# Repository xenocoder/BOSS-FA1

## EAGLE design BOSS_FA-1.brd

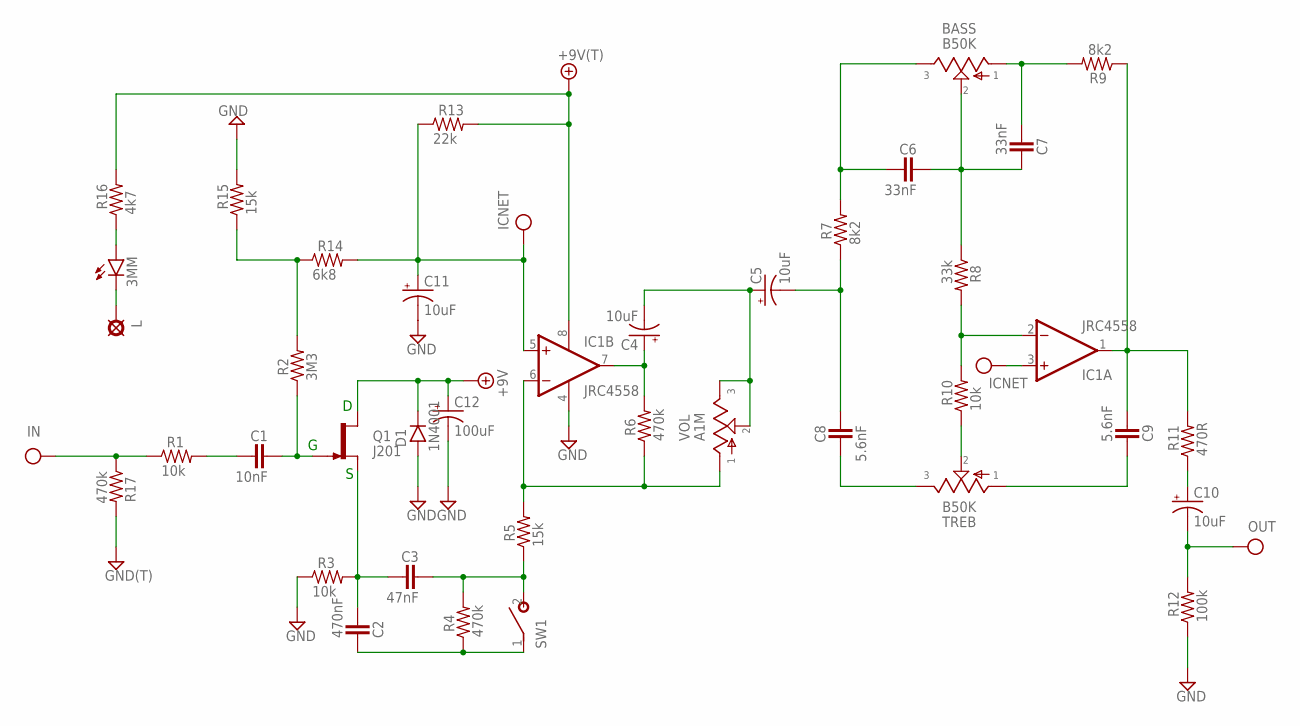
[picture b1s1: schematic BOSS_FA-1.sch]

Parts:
3MM: LED3MM
+9V: +9V(T); SQUARE
BASS: B50K; 16MM_PCB_PADS
C1: 10nF; 072X025
C2: 470nF; 072X035
C3: 47nF; 072X025
C4, C5, C10, C11: 10uF; 050_020_1
C6, C7: 33nF; 072X025
C8, C9: 5.6nF; 072X025
C12: 100uF; 063_025
D1: 1N4001; DO41-3
G: GND(T); SQUARE
IC1: JRC4558; DIL08
IN: IN(T); SQUARE
L: PAD; SQUARE
OUT: OUT(T); SQUARE
Q1: J201; TO92-
R1, R3, R10: 10k; R0207/3
R2: 3M3; R0207/3
R4, R6, R17: 470k; R0207/3
R5, R15: 15k; R0207/3
R7, R9: 8k2; R0207/3
R8: 33k; R0207/3
R11: 470R; R0207/3
R12: 100k; R0207/3
R13: 22k; R0207/3
R14: 6k8; R0207/3
R16: 4k7; R0207/3
SW1: SPST
TREB: B50K; 16MM_PCB_PADS
VOL: A1M; 16MM_PCB_PADS

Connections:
+9V: +9V.1, C12.+, D1.C, IC1.8 (V+), Q1.3 (D), R13.2, R16.2
A: C11.+, IC1.3 (+IN), IC1.5 (+IN), R13.1, R14.2
GND: C11.-, C12.-, D1.A, G.1, IC1.4 (V-), R3.1, R12.1, R15.2, R17.2
IN: IN.1, R1.1, R17.1
unnamed: C1.1, R1.2
unnamed: C1.2, Q1.1 (G), R2.1
unnamed: 3MM.A, R16.1
unnamed: R10.1, TREB.2
unnamed: C3.2, R4.2, R5.1, SW1.2 (S)
unnamed: C4.+, IC1.7 (OUT), R6.2
unnamed: IC1.6 (-IN), R5.2, R6.1, VOL.1
unnamed: 3MM.K (C), L.1
unnamed: C2.2, R4.1, SW1.1
unnamed: C2.1, C3.1, Q1.2 (S), R3.2
unnamed: C4.-, C5.+, VOL.2, VOL.3
unnamed: C5.-, C8.2, R7.1
unnamed: BASS.3, C6.1, R7.2
unnamed: BASS.2, C6.2, C7.2, R8.1
unnamed: BASS.1, C7.1, R9.2
unnamed: C9.1, IC1.1 (OUT), R9.1, R11.2
unnamed: IC1.2 (-IN), R8.2, R10.2
unnamed: C9.2, TREB.1
unnamed: C8.1, TREB.3
unnamed: C10.+, R11.1
unnamed: R2.2, R14.1, R15.1
OUT: C10.-, OUT.1, R12.2

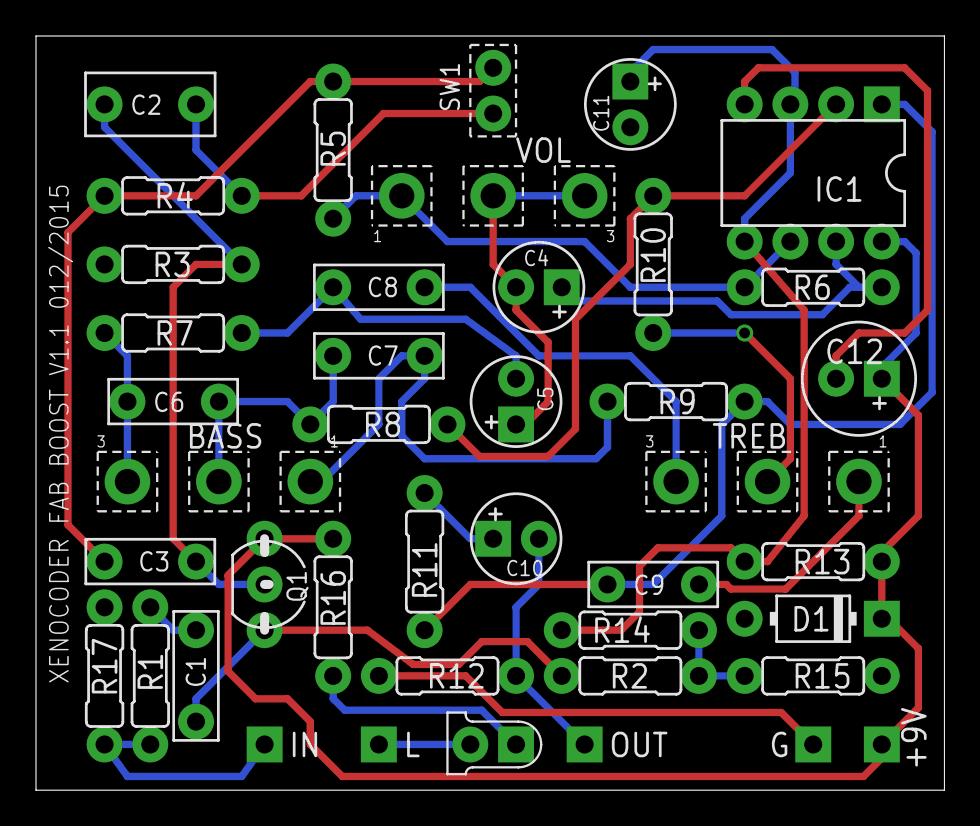
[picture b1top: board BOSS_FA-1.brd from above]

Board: 2 copper layers, 50.5 x 41.9 mm, 42 parts (0 on the bottom side), 26 nets.

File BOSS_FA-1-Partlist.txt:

Partlist

Exported from BOSS_FA-1.brd at 5/9/15 7:09 PM

EAGLE Version 7.2.0 Copyright (c) 1988-2014 CadSoft

Assembly variant: 

Part     Value          Package       Library         Position (inch)       Orientation

+9V      +9V(T)         SQUARE        mb_supply       (1.85 0.1)            R0
3MM      LED3MM         LED3MM        mb_diodes       (1 0.1)               R180
BASS     B50K           16MM_PCB_PADS mb_pots         (0.4 0.675)           R0
C1       10nF           072X025       mb_caps-box     (0.35 0.25)           R270
C2       470nF          072X035       mb_caps-box     (0.25 1.5)            R0
C3       47nF           072X025       mb_caps-box     (0.25 0.5)            R180
C4       10uF           050_020_1     mb_caps-electro (1.1 1.1)             R180
C5       10uF           050_020_1     mb_caps-electro (1.05 0.85)           R90
C6       33nF           072X025       mb_caps-box     (0.3 0.85)            R0
C7       33nF           072X025       mb_caps-box     (0.75 0.95)           R180
C8       5.6nF          072X025       mb_caps-box     (0.75 1.1)            R180
C9       5.6nF          072X025       mb_caps-box     (1.35 0.45)           R0
C10      10uF           050_020_1     mb_caps-electro (1.05 0.55)           R0
C11      10uF           050_020_1     mb_caps-electro (1.3 1.5)             R270
C12      100uF          063_025       mb_caps-electro (1.8 0.9)             R180
D1       1N4001         DO41-3        mb_diodes       (1.7 0.375)           R0
G        GND(T)         SQUARE        mb_supply       (1.7 0.1)             R0
IC1      JRC4558        DIL08         mb_ics          (1.7 1.35)            R180
IN       IN(T)          SQUARE        mb_supply       (0.5 0.1)             R0
L                       SQUARE        mb_supply       (0.75 0.1)            R0
OUT      OUT(T)         SQUARE        mb_supply       (1.2 0.1)             R0
Q1       J201           TO92-         mb_trans        (0.5 0.45)            R270
R1       10k            R0207/3       mb_resistors    (0.25 0.25)           R90
R2       3M3            R0207/3       mb_resistors    (1.3 0.25)            R0
R3       10k            R0207/3       mb_resistors    (0.3 1.15)            R0
R4       470k           R0207/3       mb_resistors    (0.3 1.3)             R180
R5       15k            R0207/3       mb_resistors    (0.65 1.4)            R270
R6       470k           R0207/3       mb_resistors    (1.7 1.1)             R0
R7       8k2            R0207/3       mb_resistors    (0.3 1)               R180
R8       33k            R0207/3       mb_resistors    (0.75 0.8)            R0
R9       8k2            R0207/3       mb_resistors    (1.4 0.85)            R180
R10      10k            R0207/3       mb_resistors    (1.35 1.15)           R90
R11      470R           R0207/3       mb_resistors    (0.85 0.5)            R270
R12      100k           R0207/3       mb_resistors    (0.9 0.25)            R0
R13      22k            R0207/3       mb_resistors    (1.7 0.5)             R0
R14      6k8            R0207/3       mb_resistors    (1.3 0.35)            R180
R15      15k            R0207/3       mb_resistors    (1.7 0.25)            R0
R16      4k7            R0207/3       mb_resistors    (0.65 0.4)            R90
R17      470k           R0207/3       mb_resistors    (0.15 0.25)           R90
SW1      SPST           SPST          mb_switches     (1 1.53)              R90
TREB     B50K           16MM_PCB_PADS mb_pots         (1.6 0.675)           R0
VOL      A1M            16MM_PCB_PADS mb_pots         (1 1.3)               R180

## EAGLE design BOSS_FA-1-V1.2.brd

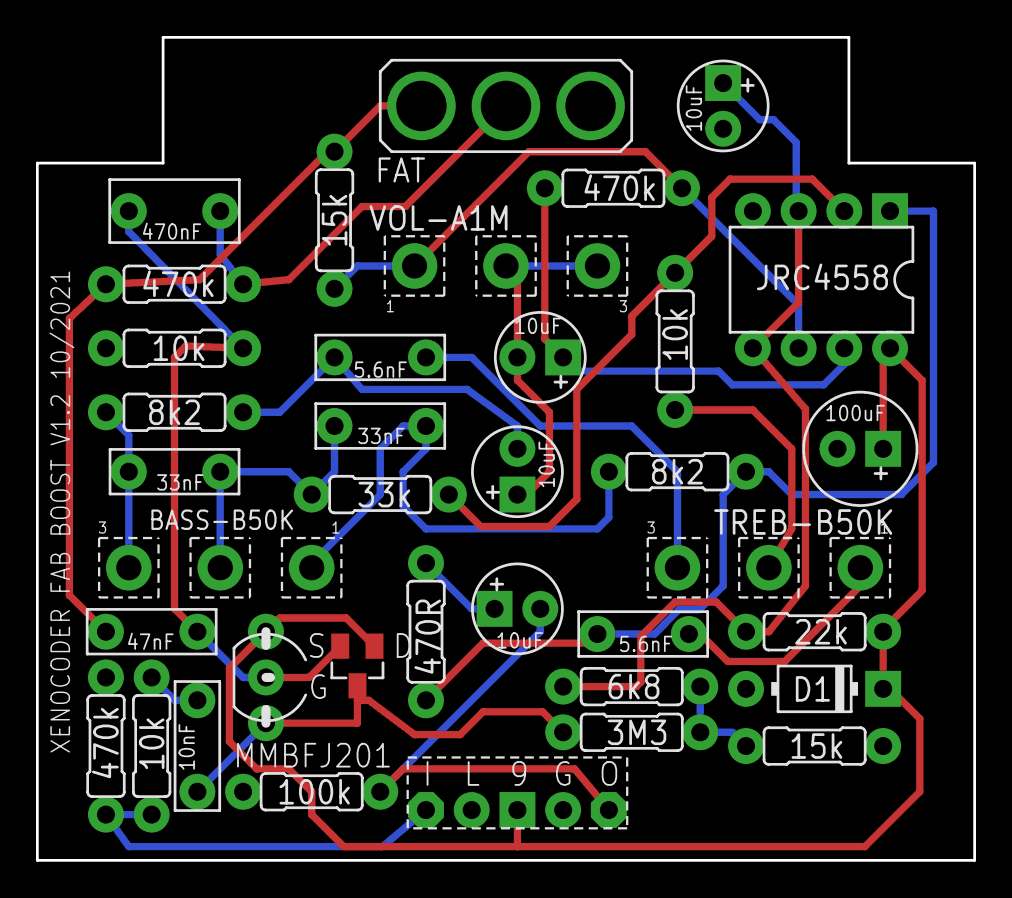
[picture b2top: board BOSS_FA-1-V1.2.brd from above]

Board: 2 copper layers, 52.1 x 45.7 mm, 37 parts (0 on the bottom side), 24 nets.

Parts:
BASS-B50K: B50K; 16MM_PCB_PADS
C1: 10nF; 072X025
C2: 470nF; 072X035
C3: 47nF; 072X025
C4, C5, C10, C11: 10uF; 050_020_1
C6, C7: 33nF; 072X025
C8, C9: 5.6nF; 072X025
C12: 100uF; 063_025
D1: 1N4001; DO41-3
FAT: M9040P
IC1: JRC4558; DIL08
MMBFJ201: SOT23
Q1: J201; TO92-
R1, R3, R10: 10k; R0207/3
R2: 3M3; R0207/3
R4, R6, R17: 470k; R0207/3
R5, R15: 15k; R0207/3
R7, R9: 8k2; R0207/3
R8: 33k; R0207/3
R11: 470R; R0207/3
R12: 100k; R0207/3
R13: 22k; R0207/3
R14: 6k8; R0207/3
TREB-B50K: B50K; 16MM_PCB_PADS
U$1: BOARDLINK
VOL-A1M: A1M; 16MM_PCB_PADS

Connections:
+9V: C12.+, D1.C, IC1.8, MMBFJ201.1, Q1.3, R13.2, U$1.3
A: C11.+, IC1.3, IC1.5, R13.1, R14.2
GND: C11.-, C12.-, D1.A, IC1.4, R3.1, R12.1, R15.2, R17.2, U$1.4
unnamed: C1.1, R1.2
unnamed: C1.2, MMBFJ201.3, Q1.1, R2.1
unnamed: R10.1, TREB-B50K.2
unnamed: C3.2, FAT.3, R4.2, R5.1
unnamed: C4.+, IC1.7, R6.2
unnamed: IC1.6, R5.2, R6.1, VOL-A1M.1
unnamed: R1.1, R17.1, U$1.1
unnamed: C2.2, FAT.2, R4.1
unnamed: C2.1, C3.1, MMBFJ201.2, Q1.2, R3.2
unnamed: C4.-, C5.+, VOL-A1M.2, VOL-A1M.3
unnamed: C5.-, C8.2, R7.1
unnamed: BASS-B50K.3, C6.1, R7.2
unnamed: BASS-B50K.2, C6.2, C7.2, R8.1
unnamed: BASS-B50K.1, C7.1, R9.2
unnamed: C9.1, IC1.1, R9.1, R11.2
unnamed: IC1.2, R8.2, R10.2
unnamed: C9.2, TREB-B50K.1
unnamed: C8.1, TREB-B50K.3
unnamed: C10.+, R11.1
unnamed: R2.2, R14.1, R15.1
unnamed: C10.-, R12.2, U$1.5

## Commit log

2015-10-08 First push of Version 1.0 files to GitHub
2015-12-30 Fixed Diode 1 orientation and connected power rail to LED (Version 1.1)
2017-12-30 Ran CAM job to get Gerber files for Seeed order
2018-01-11 Added Rough Drill Guide
2018-01-13 Cleaned up files to make version 1.1.1 release. Added drill guide.
2018-01-13 Added back dev files and made Dev branch
2018-01-27 Added build guide and updated files
2021-10-19 Version 1.2 of the FA Boost. This adds a new layout with the Boardlink
2021-10-20 Moved part names to layer 25
2021-10-20 Cleaned up save files
2021-10-22 Cleanup with drill file for V1.2 release
2025-11-22 Adds PDF and Affinity files
